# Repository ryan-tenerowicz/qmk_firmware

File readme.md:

# Lynxware Cat with trackpoint

https://www.lynxware.org/

I made some modifications to the case to work with the hardware I have. I already had some dual trackpoint code working in QMK so I made the connection wired and setup the matrix for qmk. I really like the magnetic usb cables so I carved out enough room for them. 

There's plenty of room on the inside so I was able to fit the reset circut easily.

I was able to get a much better surface finish on the keys by printing them at an angle. And I added wings to them to keep them from falling outwards because I was using smaller silent mouse switches.

https://www.lynxware.org/

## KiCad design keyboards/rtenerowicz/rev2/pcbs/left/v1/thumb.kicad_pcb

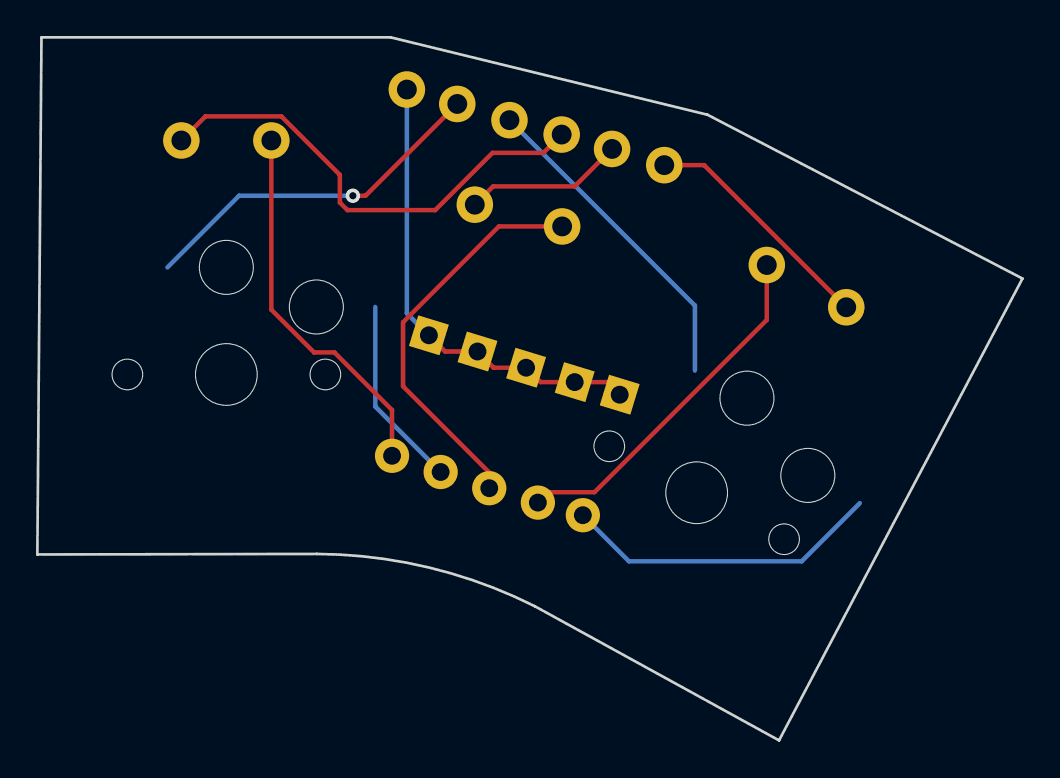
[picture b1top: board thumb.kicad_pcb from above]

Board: 2 copper layers, 54.7 x 39.1 mm, 10 parts (0 on the bottom side), 6 nets.

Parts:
D3, D4, D5, D6, D7: ComboDiode
M1, M2, M3: kailhgm
S1, S2: PG1350

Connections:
F0: D3.2, D4.2, D5.2, D6.2, D7.2
far_thumb: D7.1, S2.2
inner_thumb: D4.1, S1.2
ml_diode: D3.1, M1.2
mm_diode: D6.1, M2.2
mr_diode: D5.1, M3.1

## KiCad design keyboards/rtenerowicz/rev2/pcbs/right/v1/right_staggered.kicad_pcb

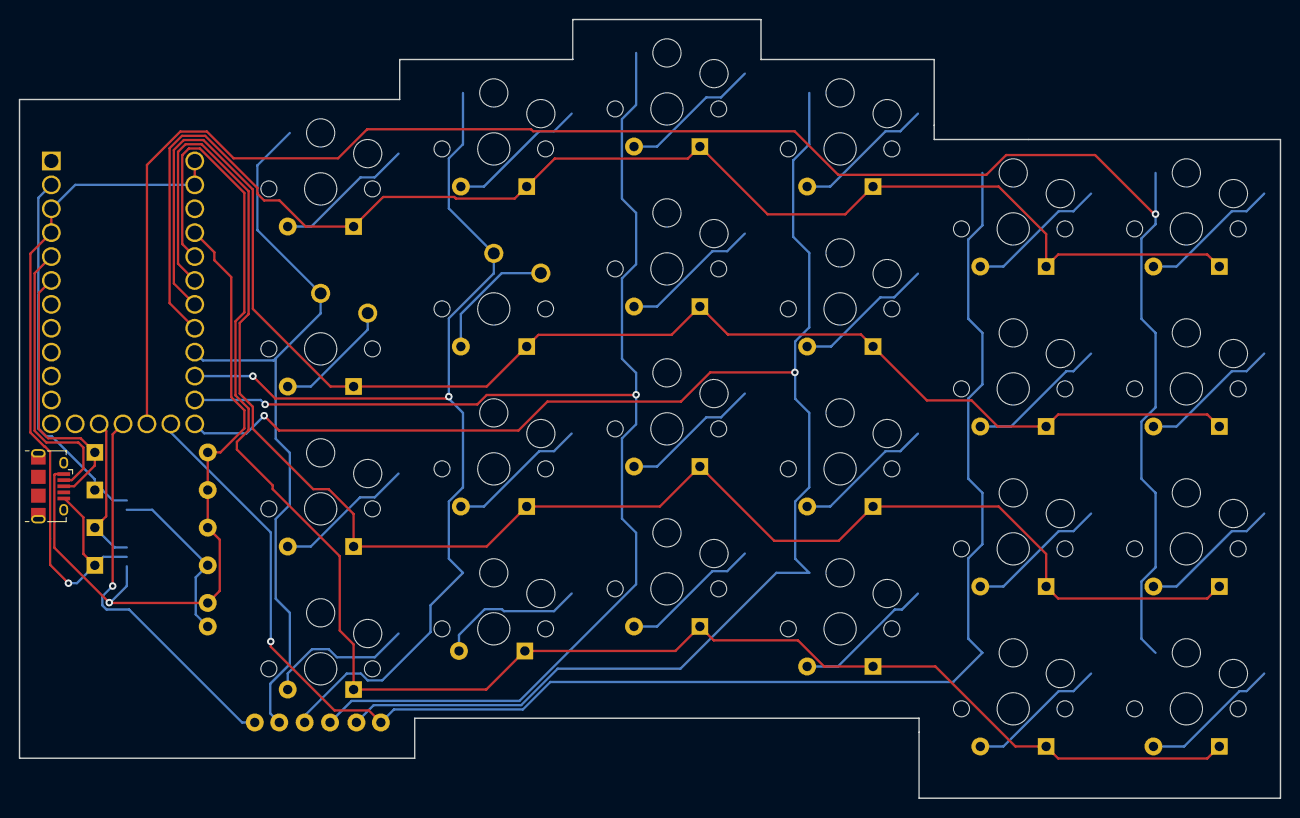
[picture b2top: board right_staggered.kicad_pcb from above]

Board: 2 copper layers, 134.0 x 82.8 mm, 52 parts (0 on the bottom side), 35 nets.

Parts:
D1, D2, D3, D4, D5, D6, D7, D8, D9, D10, D11, D12, D13, D14, D15, D16, D17, D18, D19, D20, D21, D22, D23, D24, D25, D26, D27, D28: ComboDiode
S1, S2, S3, S4, S5, S6, S7, S8, S9, S10, S11, S12, S13, S14, S15, S16, S17, S18, S19, S20, S21, S22, S23, S24: PG1350

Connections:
B1: S1.2, S3.1, S4.1, S5.1
B2: S9.1, S10.1, S11.1, S12.1
B3: S2.2, S6.1, S7.1, S8.1
B6: S13.1, S14.1, S15.1, S16.1
F0: S17.1, S18.1, S19.1, S20.1
F1: S21.1, S22.1, S23.1, S24.1
F4: D1.2, D5.2, D9.2, D13.2, D17.2, D21.2
F5: D2.2, D6.2, D10.2, D14.2, D18.2, D22.2
F6: D3.2, D7.2, D11.2, D15.2, D19.2, D23.2
F7: D4.2, D8.2, D12.2, D16.2, D20.2, D24.2
VCC: D25.1, D26.1, D27.1
index_bottom: D5.1, S6.2
index_home: D6.1, S7.2
index_nums: D8.1, S8.2
index_top: D7.1, S2.1
inner_bottom: D1.1, S3.2
inner_home: D2.1, S4.2
inner_nums: D4.1, S5.2
inner_top: D3.1, S1.1
middle_bottom: D9.1, S9.2
middle_home: D10.1, S10.2
middle_nums: D12.1, S12.2
middle_top: D11.1, S11.2
outer_bottom: D21.1, S21.2
outer_home: D22.1, S22.2
outer_nums: D24.1, S24.2
outer_top: D23.1, S23.2
pinky_bottom: D17.1, S17.2
pinky_home: D18.1, S18.2
pinky_nums: D20.1, S20.2
pinky_top: D19.1, S19.2
ring_bottom: D13.1, S13.2
ring_home: D14.1, S14.2
ring_nums: D16.1, S16.2
ring_top: D15.1, S15.2

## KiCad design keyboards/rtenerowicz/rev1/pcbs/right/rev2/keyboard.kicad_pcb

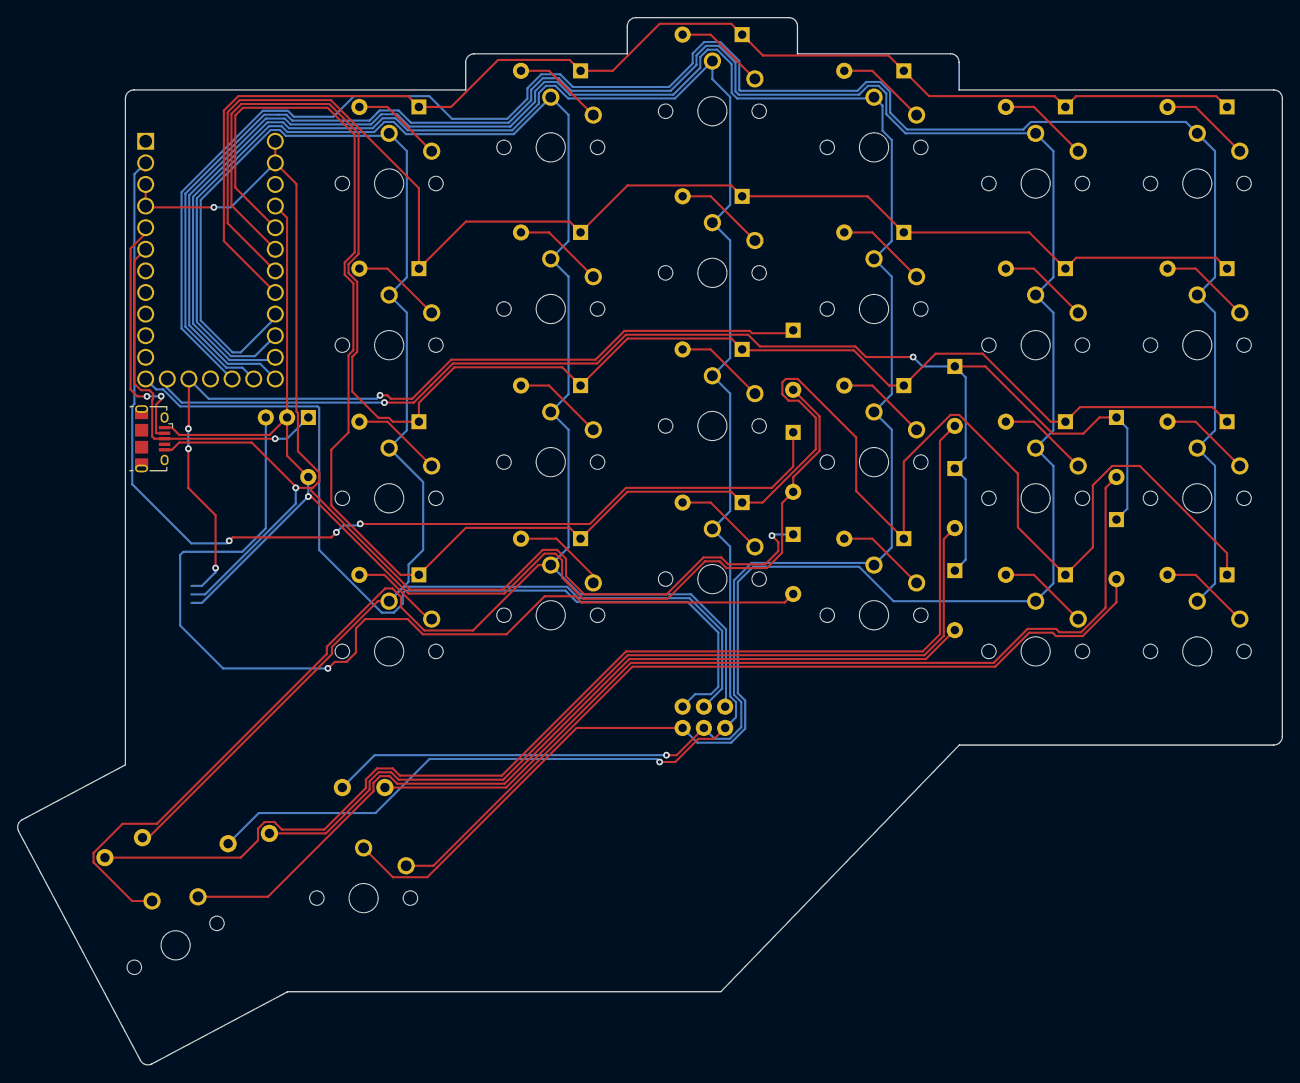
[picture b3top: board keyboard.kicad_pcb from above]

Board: 2 copper layers, 148.7 x 123.1 mm, 63 parts (0 on the bottom side), 41 nets.

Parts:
D1, D2, D3, D4, D5, D6, D7, D8, D9, D10, D11, D12, D13, D14, D15, D16, D17, D18, D19, D20, D21, D22, D23, D24, D27, D28, D29, D30, D31, D32, D33, D34, D36: ComboDiode
D35: fiveway
M1, M2, M3: kailhgm
S1, S2, S3, S4, S5, S6, S7, S8, S9, S10, S11, S12, S13, S14, S15, S16, S17, S18, S19, S20, S21, S22, S23, S24, S25, S26: PG1350

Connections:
B1: D35.4, M3.2, S1.2, S2.2, S3.2, S4.2
B2: D35.2, M2.1, S9.2, S10.2, S11.2, S12.2
B3: D35.5, S5.2, S6.2, S7.2, S8.2, S26.2
B6: D35.1, M1.1, S13.2, S14.2, S15.2, S16.2
B7: D27.2, D28.2, D29.2, D30.2, D31.2
F0: D35.0, S17.2, S18.2, S19.2, S20.2, S25.2
F1: S21.2, S22.2, S23.2, S24.2
F4: D1.2, D5.2, D9.2, D13.2, D17.2, D21.2
F5: D2.2, D6.2, D10.2, D14.2, D18.2, D22.2
F6: D3.2, D7.2, D11.2, D15.2, D19.2, D23.2
F7: D4.2, D8.2, D12.2, D16.2, D20.2, D24.2
VCC: D33.1, D34.1, D36.1
far_thumb: D31.1, S26.1
index_bottom: D5.1, S5.1
index_home: D6.1, S6.1
index_nums: D8.1, S8.1
index_top: D7.1, S7.1
inner_bottom: D1.1, S1.1
inner_home: D2.1, S2.1
inner_nums: D4.1, S4.1
inner_thumb: D28.1, S25.1
inner_top: D3.1, S3.1
middle_bottom: D9.1, S9.1
middle_home: D10.1, S10.1
middle_nums: D12.1, S12.1
middle_top: D11.1, S11.1
ml_diode: D27.1, M1.2
mm_diode: D30.1, M2.2
mr_diode: D29.1, M3.1
outer_bottom: D21.1, S21.1
outer_home: D22.1, S22.1
outer_nums: D24.1, S24.1
outer_top: D23.1, S23.1
pinky_bottom: D17.1, S17.1
pinky_home: D18.1, S18.1
pinky_nums: D20.1, S20.1
pinky_top: D19.1, S19.1
ring_bottom: D13.1, S13.1
ring_home: D14.1, S14.1
ring_nums: D16.1, S16.1
ring_top: D15.1, S15.1

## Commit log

2021-11-06 Remove outdated comments.
2022-07-12 Remove some unneeded comments
2022-07-12 Remove unneeded comment
2023-03-08 Preliminry support for rp2040/Elite-Pi. No Trackpoint support yet.
2023-03-08 gamelaster:ps2-pio PR merge (#22)
    * [Core] PS/2 PIO Driver for RP2040
    * Init pins in code instead of PIO
    * Use ChibiOS input buffer queue instead own ring buffer
    * Unify ps2_host_recv_response
    * Change ps2_host_send fifo check sequence + add forgotten sys unlock
    * Fix formatting
2023-03-14 trying to get TP support working on Elite-Pi/rp2040
2023-03-23 Bump actions/stale from 5 to 8
    Bumps [actions/stale](https://github.com/actions/stale) from 5 to 8.
    - [Release notes](https://github.com/actions/stale/releases)
    - [Changelog](https://github.com/actions/stale/blob/main/CHANGELOG.md)
    - [Commits](https://github.com/actions/stale/compare/v5...v8)
    ---
    updated-dependencies:
2023-11-27 rtenerowicz/rev1 initally builds
2023-11-27 rev1 cruft removed
2023-11-27 single trackpoint works
2023-11-27 pointing device builds ps2 copy
2023-11-28 working driver
2023-11-28 split keyboard
2023-11-28 working single split trackpoint
2023-11-29 working double trackpoint
2023-12-06 left pcb
2023-12-06 left input file
2023-12-13 pcb rev2
2023-12-31 toggle scroll
2024-01-02 keymap
2024-03-31 half joystick lynx working
2024-04-16 working side trackpoint
2024-04-18 matrix
2024-04-21 lynxware matrix done
2024-04-30 readme
2024-04-30 images
2024-06-02 save
2024-06-19 update
    update 2
